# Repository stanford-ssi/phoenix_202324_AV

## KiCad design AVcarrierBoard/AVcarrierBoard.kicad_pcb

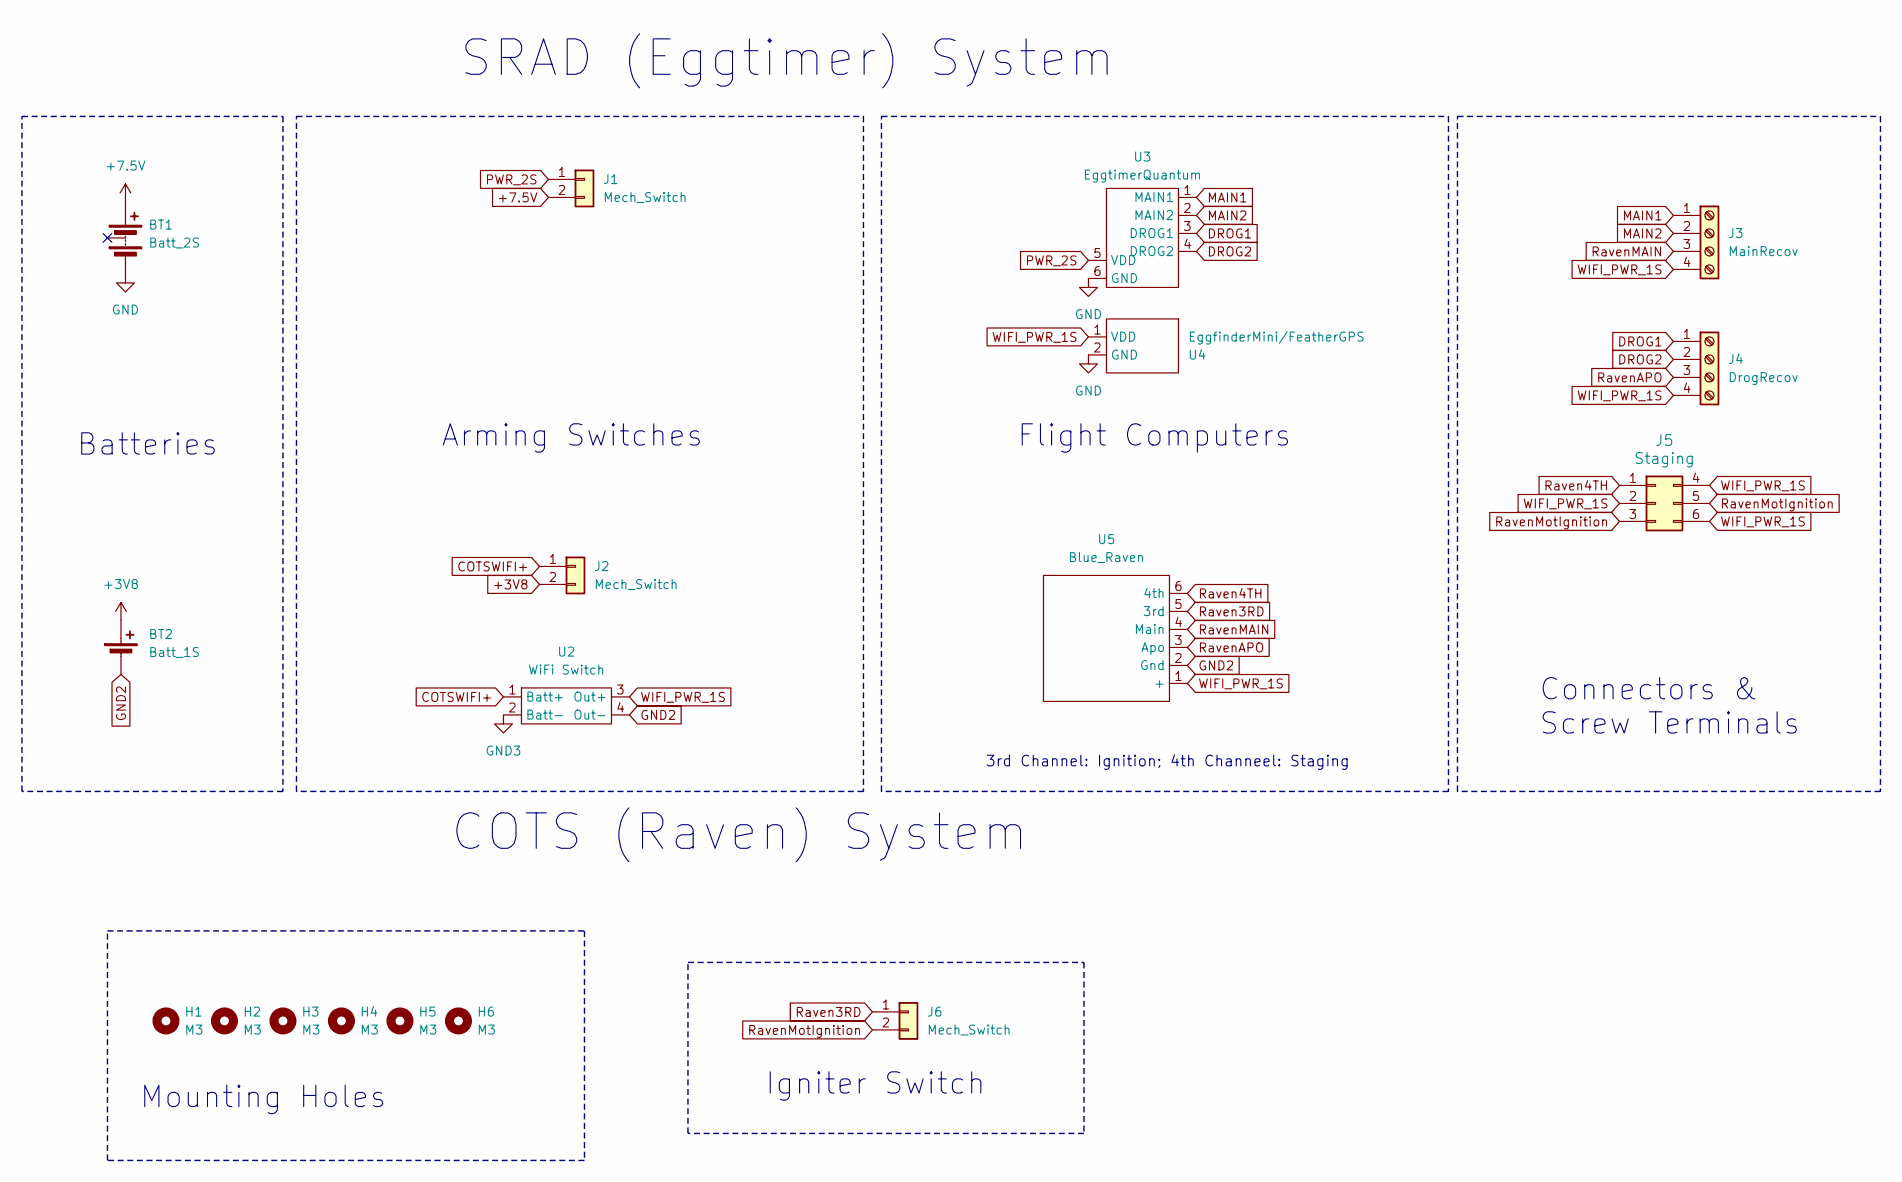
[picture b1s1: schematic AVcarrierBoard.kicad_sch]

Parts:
BT1: Batt_2S; BAT_1048P
BT2: Batt_1S; 1042P_KEY
H1, H2, H3, H4, H5, H6: M3; MountingHole_3.2mm_M3_ISO14580
J1, J2, J6: Mech_Switch; CON_436500227_MOL
J3: MainRecov; TE_282837-4-2
J4: DrogRecov; TE_282837-4
J5: Staging; CON_462070006
U2: WiFi Switch; Eggtime_WiFi_switch
U3: EggtimerQuantum
U4: EggfinderMini/FeatherGPS; Featherweight_GPS
U5: Blue_Raven; Blue Raven

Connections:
+3V8: BT2.1 (+), J2.2
+7.5V: BT1.1 (+), J1.2
COTSWIFI+: J2.1, U2.1 (Batt+)
DROG1: J4.1, U3.3 (DROG1)
DROG2: J4.2, U3.4 (DROG2)
GND: BT1.3 (-), U3.6 (GND), U4.2 (GND)
GND2: BT2.2 (-), U2.4 (Out-), U5.2 (Gnd)
GND3: U2.2 (Batt-)
MAIN1: J3.1, U3.1 (MAIN1)
MAIN2: J3.2, U3.2 (MAIN2)
PWR_2S: J1.1, U3.5 (VDD)
Raven3RD: J6.1, U5.5 (3rd)
Raven4TH: J5.1, U5.6 (4th)
RavenAPO: J4.3, U5.3 (Apo)
RavenMAIN: J3.3, U5.4 (Main)
RavenMotIgnition: J5.3, J5.5, J6.2
WIFI_PWR_1S: J3.4, J4.4, J5.2, J5.4, J5.6, U2.3 (Out+), U4.1 (VDD), U5.1 (+)

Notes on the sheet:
3rd Channel: Ignition; 4th Channeel: Staging
SRAD (Eggtimer) System
Arming Switches
COTS (Raven) System
Mounting Holes
Connectors & Screw Terminals
Igniter Switch
Flight Computers
Batteries

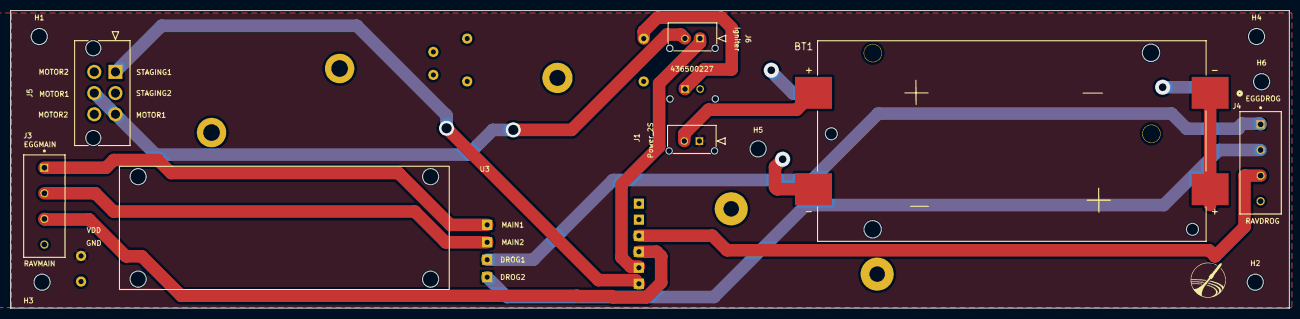
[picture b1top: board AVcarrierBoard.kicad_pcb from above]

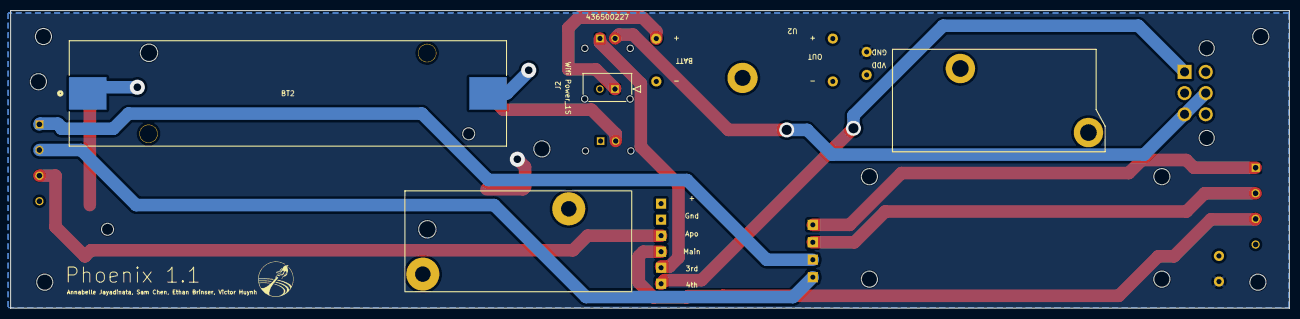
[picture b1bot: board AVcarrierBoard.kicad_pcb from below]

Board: 4 copper layers, 253.6 x 59.0 mm, 18 parts (5 on the bottom side), 16 nets.

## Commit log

2024-02-22 blue raven symbol and footprint
2024-02-22 Eggtimer Quark symbol and footprint files
2024-02-22 Create Featherweight_GPS.kicad_mod
    eyeballing
2024-02-27 created project and Featherweight GPS symbol
2024-02-27 new files for blue raven
2024-02-27 created footprint libarary
2024-02-27 updated footprints from other comits
2024-02-27 featherweight GPS fixes
2024-02-27 Eggfinder Mini footprint
2024-02-27 EggdfinderMini symbol
2024-02-29 Updated symbol library
2024-02-29 Added Eggtimer WiFi switch symbol to library
2024-02-29 Added WiFi switch footprint and some courtyards
2024-02-29 LOST FILES HAHAAHAHA
2024-02-29 Create .gitignore
    This should fix the fp-info-cache issues
2024-02-29 Added wifi switch into schematic
2024-03-05 Created PCB, linked 3D step files to footprints, and laid out board (10 inch length)
2024-03-07 ok ok
2024-03-14 edited
2024-03-14 editedd
2024-03-26 Schematic updated based on Ethan's review
2024-03-26 Added additional igniter switch, replaced quark with quantum, and updated PCB
2024-03-26 Updated PCB, made new nets and vias according to last change. Did not fill power layers yet.
2024-03-26 Updated PCB further to avoid any DRC errors and missed connections
2024-03-26 More PCB changes according to Ethan's review
2024-03-26 Final DRC warning resolved
2024-03-26 Added logo and creator names. Need a more creative name plz
2024-03-27 Updated author names and added missing footprint
2024-03-27 Rerouted footprint directory
2024-04-01 Fixed errors and modified board based on comments made by Ethan on Mar 30
2024-04-02 final edits made, order placed
2024-04-05 Changed quantum hole locations
2024-04-05 payload code
2024-04-05 fixed
2024-04-05 Update scd4x_i2c_example_usage.c
    Added command to write into file. Might need debugging.
2024-04-09 Changed hole sizes based on 4/1 and 4/4 feedback
    Still need to add holes for 3D printed battery mount
2024-04-09 Added step file for battery holder design
2024-04-09 Modified the board again to make battery mount design easier
2024-04-09 Changed mount hole pad sizes
2024-04-09 Decluttered folder
2024-04-09 Solved DRC
2024-04-09 Changed location of 1S battery and remade STEP
2024-04-15 Added mounting holes for battery holders
2024-04-16 fix a bit
2024-04-23 changes to blue raven orientation, radio power, wifi gnd, etc.
2024-04-23 3d model for molex connectors done.
2024-04-23 board ordered, with gerber files
2024-05-16 camera code
